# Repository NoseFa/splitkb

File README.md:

# Nordic split

A split low-profile wireless keyboard with a nordic ISO layout. I used the [Caldera Keyboard by Christian Selig](https://github.com/christianselig/caldera-keyboard) as inspiration and it clearly shows in the design. Still the keyboard uses a nice!nano like microcontroller based on the same NRF52840, ZMK as the firmware and a custom pcb with Choc V1 hotswap sockets. The keyboard also has an ortholinear layout which can be more ergonomic for some users.

The project was made and designed as a part of Hack Club's [Fallout](https://fallout.hackclub.com/) event where people make hardware projects and get a chance to go to Shenzhen, China. This was also one of my first electronics projects.

## Highlights

* Hotswapping
* Open-source
* ZMK firmware (ZMK studio support)
* Wireless
* Nordic layout
* total of 74 keys

## Why it exists?

The project was made because I wanted a split keyboard but needed a nordic layout for my day to day stuff (I need the letters Ä, Ö, Å). So the nordic split was born. I took inspiration from the Caldera keyboard by Christian Selig. It's low profile so it can be transported easily around and it's also wireless so no need for annoying dual or split cables for connecting to a computer or laptop.

This is the first keyboard I have designed so the keymap and layout were made with some educated guess work. They might be updated later down the line. I will update this repo with the most recent keymap I use. Even though it was designed as nordic layout first. The keyboard could also be used by people with non-nordic layouts and you could use the extra row of keys on the right side as shortcut or macro keys. Of course also the pcb could be edited and these keys removed if you don't want them. This keyboard has ZMK studio support so you can change the keymap in the [ZMK.studio](https://zmk.studio) web app.

## BOM summary

* Pro Micro NRF52840 [Aliexpress](https://www.aliexpress.com/item/1005007205026373.html?spm=a2g0o.productlist.main.8.5285a54cPOmIpa&aem_p4p_detail=202603200108531573820844269200000457052&algo_pvid=ebbbcca8-17d4-4ca8-b59a-75b1f3198b0b&algo_exp_id=ebbbcca8-17d4-4ca8-b59a-75b1f3198b0b-7&pdp_ext_f=%7B%22order%22%3A%22771%22%2C%22eval%22%3A%221%22%2C%22fromPage%22%3A%22search%22%7D&pdp_npi=6%40dis%21EUR%214.49%213.16%21%21%2134.88%2124.54%21%40211b813f17739941330401522ee8fd%2112000039797470328%21sea%21FI%210%21ABX%211%210%21n_tag%3A-29910%3Bd%3Ab451bb2c%3Bm03_new_user%3A-29895%3BpisId%3A5000000197850273&curPageLogUid=OxA2oroU7gov&utparam-url=scene%3Asearch%7Cquery_from%3A%7Cx_object_id%3A1005007205026373%7C_p_origin_prod%3A&search_p4p_id=202603200108531573820844269200000457052_2)
* Kailh choc v1 low-profile switches [Aliexpress](https://www.aliexpress.com/item/1005008644185126.html?spm=a2g0o.productlist.main.5.adcaQGvpQGvpZu&algo_pvid=7020f10a-7006-45f4-a42f-99f6c67908cb&algo_exp_id=7020f10a-7006-45f4-a42f-99f6c67908cb-4&pdp_ext_f=%7B%22order%22%3A%2284%22%2C%22eval%22%3A%221%22%2C%22fromPage%22%3A%22search%22%7D&pdp_npi=6%40dis%21EUR%219.09%216.67%21%21%2169.58%2151.07%21%40211b655217816346214237590eeae4%2112000046073107251%21sea%21FI%210%21ABX%211%210%21n_tag%3A-29910%3Bd%3Ab451bb2c%3Bm03_new_user%3A-29895%3BpisId%3A5000000206890820&curPageLogUid=ON5BcLwWvUu1&utparam-url=scene%3Asearch%7Cquery_from%3A%7Cx_object_id%3A1005008644185126%7C_p_origin_prod%3A)
* 304050 Lithium-Polymer battery [42Keebs.eu](https://42keebs.eu/shop/parts/lithium-polymer-battery/?attribute_size=304050%20(600%20mAh))
* Kailh Low Profile Choc hotswap sockets [Aliexpress](https://www.aliexpress.com/item/1005011893351142.html?spm=a2g0o.productlist.main.20.799300h000h08H&algo_pvid=3ed31f2b-68fe-441b-8d77-a491477a4d1e&algo_exp_id=3ed31f2b-68fe-441b-8d77-a491477a4d1e-19&pdp_ext_f=%7B%22order%22%3A%2213%22%2C%22spu_best_type%22%3A%22price%22%2C%22eval%22%3A%221%22%2C%22fromPage%22%3A%22search%22%7D&pdp_npi=6%40dis%21EUR%212.21%210.87%21%21%2116.92%216.67%21%402103894417816348652316185eb3fb%2112000056929014932%21sea%21FI%210%21ABX%211%210%21n_tag%3A-29910%3Bd%3Ab451bb2c%3Bm03_new_user%3A-29895%3BpisId%3A5000000206890820&curPageLogUid=nRsxJkAXhesI&utparam-url=scene%3Asearch%7Cquery_from%3A%7Cx_object_id%3A1005011893351142%7C_p_origin_prod%3A)
* PCB [JLCPCB](https://cart.jlcpcb.com/quote?spm=jlcpcb.Public.2006)
* M2x8mm screws [Aliexpress](https://www.aliexpress.com/item/1005006995421098.html?spm=a2g0o.productlist.main.2.57264ed6EljEJ5&algo_pvid=026d2a42-6c71-4858-96d8-406083879f60&algo_exp_id=026d2a42-6c71-4858-96d8-406083879f60-1&pdp_ext_f=%7B%22order%22%3A%2222176%22%2C%22eval%22%3A%221%22%2C%22orig_sl_item_id%22%3A%221005006995421098%22%2C%22orig_item_id%22%3A%221005006674812661%22%2C%22fromPage%22%3A%22search%22%7D&pdp_npi=6%40dis%21EUR%214.63%210.86%21%21%2136.22%216.66%21%402103956b17767083060128755e3ad9%2112000038985462862%21sea%21FI%210%21ABX%211%210%21n_tag%3A-29910%3Bd%3A2599385b%3Bm03_new_user%3A-29895%3BpisId%3A5000000205009259&curPageLogUid=HEtOGF0Rf2DI&utparam-url=scene%3Asearch%7Cquery_from%3A%7Cx_object_id%3A1005006995421098%7C_p_origin_prod%3A1005006674812661#nav-specification)
* M2 3mm OD heated inserts [Aliexpress](https://www.aliexpress.com/item/1005006071488810.html?spm=a2g0o.productlist.main.4.3d84TPXMTPXMy9&aem_p4p_detail=202606081050152534281587616560004055138&algo_pvid=06543870-17ef-47a2-afb1-9c8174047a0e&algo_exp_id=06543870-17ef-47a2-afb1-9c8174047a0e-3&pdp_ext_f=%7B%22order%22%3A%2222568%22%2C%22spu_best_type%22%3A%22price%22%2C%22eval%22%3A%221%22%2C%22fromPage%22%3A%22search%22%7D&pdp_npi=6%40dis%21EUR%212.84%211.82%21%21%2121.70%2113.93%21%40211b80d117809410151605687ea277%2112000035595774900%21sea%21FI%210%21ABX%211%210%21n_tag%3A-29910%3Bd%3Ab451bb2c%3Bm03_new_user%3A-29895%3BpisId%3A5000000207307501&curPageLogUid=m7Avo8Kp89dD&utparam-url=scene%3Asearch%7Cquery_from%3A%7Cx_object_id%3A1005006071488810%7C_p_origin_prod%3A&search_p4p_id=202606081050152534281587616560004055138_1)
* SOD-123 Diodes [Aliexpress](https://www.aliexpress.com/item/1005007536719404.html?spm=a2g0o.productlist.main.2.7a4f7cffMh3WoE&algo_pvid=ce6776f4-195e-458e-a30a-b94edfc8714d&algo_exp_id=ce6776f4-195e-458e-a30a-b94edfc8714d-1&pdp_ext_f=%7B%22order%22%3A%2294%22%2C%22eval%22%3A%221%22%2C%22fromPage%22%3A%22search%22%7D&pdp_npi=6%40dis%21EUR%211.87%211.43%21%21%2114.28%2110.91%21%40210385db17816331963967914e2c50%2112000041199095476%21sea%21FI%210%21ABX%211%210%21n_tag%3A-29910%3Bd%3Ab451bb2c%3Bm03_new_user%3A-29895%3BpisId%3A5000000207307454&curPageLogUid=43hY8FWrAoHt&utparam-url=scene%3Asearch%7Cquery_from%3A%7Cx_object_id%3A1005007536719404%7C_p_origin_prod%3A)
* Kailh choc V1 A keycaps [Aliexpress](https://www.aliexpress.com/item/1005009262759706.html?spm=a2g0o.productlist.main.34.2b272264TTHKbg&algo_pvid=d5ef2f18-90d5-413f-95b3-76c1146a87f9&algo_exp_id=d5ef2f18-90d5-413f-95b3-76c1146a87f9-33&pdp_ext_f=%7B%22order%22%3A%22207%22%2C%22eval%22%3A%221%22%2C%22fromPage%22%3A%22search%22%7D&pdp_npi=6%40dis%21EUR%2127.60%2119.32%21%21%21211.53%21148.07%21%40211b6c1717816979752355472ea7cb%2112000048523171763%21sea%21FI%210%21ABX%211%210%21n_tag%3A-29910%3Bd%3A2599385b%3Bm03_new_user%3A-29895&curPageLogUid=vcYL3e40gH5n&utparam-url=scene%3Asearch%7Cquery_from%3A%7Cx_object_id%3A1005009262759706%7C_p_origin_prod%3A)
* Anti-slip pads [Aliexpress](https://www.aliexpress.com/item/1005007438396940.html?spm=a2g0o.detail.pcDetailTopMoreOtherSeller.4.d2f1TEEKTEEKp1&gps-id=pcDetailTopMoreOtherSeller&scm=1007.40050.354490.0&scm_id=1007.40050.354490.0&scm-url=1007.40050.354490.0&pvid=88a60b80-e045-479f-a4ac-5c6461aae76d&_t=gps-id%3ApcDetailTopMoreOtherSeller%2Cscm-url%3A1007.40050.354490.0%2Cpvid%3A88a60b80-e045-479f-a4ac-5c6461aae76d%2Ctpp_buckets%3A668%232846%238112%231997&pdp_ext_f=%7B%22order%22%3A%22241%22%2C%22eval%22%3A%221%22%2C%22sceneId%22%3A%2230050%22%2C%22fromPage%22%3A%22recommend%22%7D&pdp_npi=6%40dis%21EUR%213.13%210.87%21%21%213.55%210.99%21%4021039eb717816998437457301e1070%2112000040757551361%21rec%21FI%21%21ABX%211%210%21n_tag%3A-29910%3Bd%3A2599385b%3Bm03_new_user%3A-29895%3BpisId%3A5000000206890820&utparam-url=scene%3ApcDetailTopMoreOtherSeller%7Cquery_from%3A%7Cx_object_id%3A1005007438396940%7C_p_origin_prod%3A)

Total price for the whole build excluding 3d prints is 159.26€.

You can find the full [BOM here](BOM.csv). It includes pricing, amount of parts, extra info etc.

## Build Guide Summary

1. Order PCB and other parts.
2. Order or print the case.
3. Solder parts to the PCBs (Diodes, hotswap-sockets, microcontroller)
4. Install the heated threaded inserts to the spots in the case (4 per side)
5. Install the PCB to the case.
6. Install top plate.
7. Install the choc switches to the sockets and keycaps.
8. Flash software (Check software section)
9. Enjoy!

More detailed build guide is available in the [build guide.md file](buildGuide.md).

## Software

See [Software.md](./Software/software.md) for more info about software and software installation instructions. The software source code files are in a different repo ([NoseFa/nordic-split-zmk](https://github.com/NoseFa/nordic-split-zmk))

## PCB

Here is a picture of the left side PCB. You can see the switches, traces and a spot for the microcontrollers. The PCBs are seperated by mouse bites in the middle. Unlike some other split keyboards the Nordic Splits halves aren't mirrored but instead the right side has an extra row of keys primarly needed to support the Nordic layout.

The pcb was designed in KiCad by me. You can view the files in the [Kicad folder](./KICAD/splitkb).

Here is also the schematic which is split into three different pages. One for each side and one main page that has the mousebites and links the pages together.

For ordering the PCB I used JLCPCB. You can find the gerber files as a zip in the [Production files folder](./KICAD/ProductionFiles/NordicSplitGerber.zip)

## 3D files

3d Files are seperated into 2 folders. Full project which has the .fz3 and .step versions of the whole 3D project. The PCB was exported when I finished the the edge cuts so some holes next to the micro controller might be different. I didn't include the microcontroller or the SMD diodes in the 3d project but I did check that they fit.

The 3d files for the switches in the Fusion project are from [printables](https://www.printables.com/model/716753-kaliah-choc-v1-v2-dummy/files). They are made by [cobypear](https://www.printables.com/@cobypear_1543945). They are originally from the same library as I used in kicad which is the [kiswitch library](https://github.com/kiswitch/kiswitch/tree/main/library/3dmodels/3d-library.3dshapes). You can find the original files from the link.

## Zine Page

Zine page is also available as a [PDF](./ZinePage/ZinePage.pdf).
Background picture was taken by my dad when we went up north.

## Demo

A video of the keyboard in use.

SOON (When I get the parts).

## Acknowledgements

* Thanks to [Hack Club](https://hackclub.com/) [Fallout](https://fallout.hackclub.com/). If you want to view the project I made for Fallout including journals you can view it on [the event page](https://fallout.hackclub.com/projects/156).

* [Caldera Keyboard by Christian Selig](https://github.com/christianselig/caldera-keyboard) was used as inspiration and [his video](https://www.youtube.com/watch?v=7UXsD7nSfDY) was a great watch. My design is clearly inspired by him.

## Tools used

### Design

* [KiCad](https://www.kicad.org/) (PCB design)
* [Fusion](https://www.autodesk.com/products/fusion-360/personal) (Case design)
* [Excalidraw](https://app.excalidraw.com/) (Notetaking)
* [ZMK CLI](https://zmk.dev/docs/zmk-cli) (Firmware creation)

### Assembly

* Soldering iron
* Screwdriver for the M2 screws
* Computer to flash the software.
* USB-C cable

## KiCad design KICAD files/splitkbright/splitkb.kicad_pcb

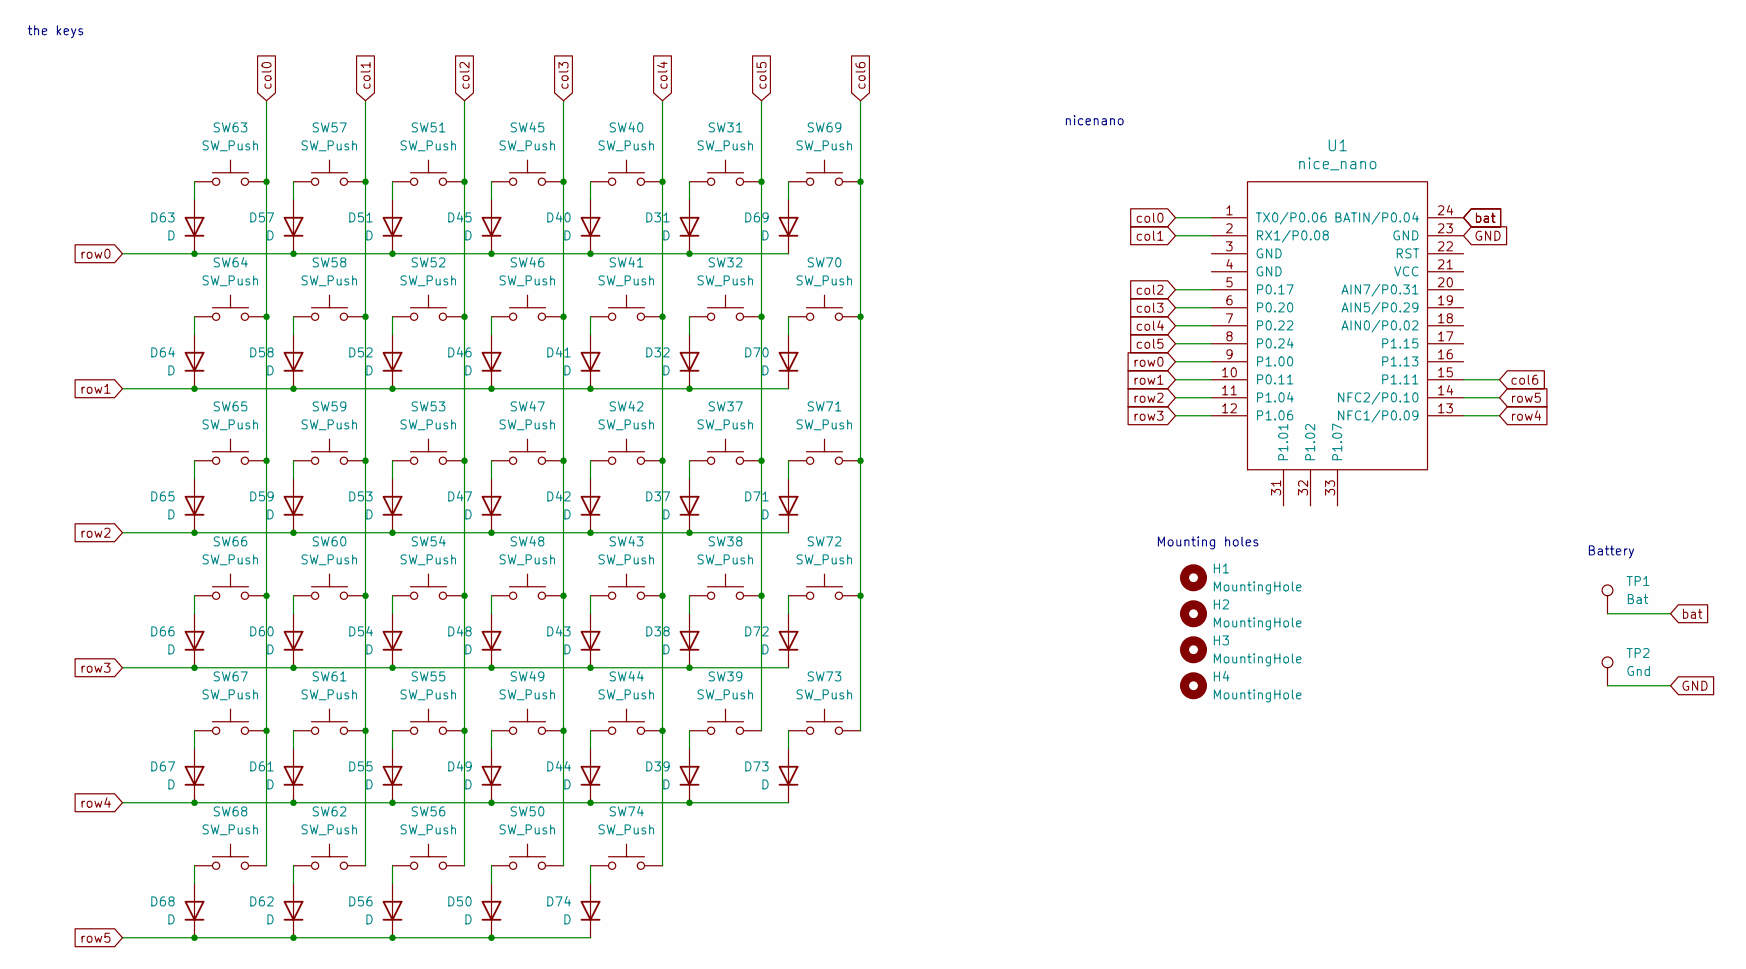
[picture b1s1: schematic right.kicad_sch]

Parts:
D31, D32, D37, D38, D39, D40, D41, D42, D43, D44, D45, D46, D47, D48, D49, D50, D51, D52, D53, D54, D55, D56, D57, D58, D59, D60, D61, D62, D63, D64, D65, D66, D67, D68, D69, D70, D71, D72, D73, D74: D; D_SOD-123
H1, H2, H3, H4: MountingHole
SW31, SW32, SW37, SW38, SW39, SW40, SW41, SW42, SW43, SW44, SW45, SW46, SW47, SW48, SW49, SW50, SW51, SW52, SW53, SW54, SW55, SW56, SW57, SW58, SW59, SW60, SW61, SW62, SW63, SW64, SW65, SW66, SW67, SW68, SW69, SW70, SW71, SW72, SW73, SW74: SW_Push; SW_Hotswap_Kailh_Choc_V1V2
TP1: Bat; TestPoint_Pad_D2.0mm
TP2: Gnd; TestPoint_Pad_D2.0mm
U1: nice_nano

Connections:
GND: TP2.1, U1.23 (GND)
unnamed: D31.2 (A), SW31.2
unnamed: D32.2 (A), SW32.2
unnamed: D37.2 (A), SW37.2
unnamed: D38.2 (A), SW38.2
unnamed: D39.2 (A), SW39.2
unnamed: D40.2 (A), SW40.2
unnamed: D41.2 (A), SW41.2
unnamed: D42.2 (A), SW42.2
unnamed: D43.2 (A), SW43.2
unnamed: D44.2 (A), SW44.2
unnamed: D45.2 (A), SW45.2
unnamed: D46.2 (A), SW46.2
unnamed: D47.2 (A), SW47.2
unnamed: D48.2 (A), SW48.2
unnamed: D49.2 (A), SW49.2
unnamed: D50.2 (A), SW50.2
unnamed: D51.2 (A), SW51.2
unnamed: D52.2 (A), SW52.2
unnamed: D53.2 (A), SW53.2
unnamed: D54.2 (A), SW54.2
unnamed: D55.2 (A), SW55.2
unnamed: D56.2 (A), SW56.2
unnamed: D57.2 (A), SW57.2
unnamed: D58.2 (A), SW58.2
unnamed: D59.2 (A), SW59.2
unnamed: D60.2 (A), SW60.2
unnamed: D61.2 (A), SW61.2
unnamed: D62.2 (A), SW62.2
unnamed: D63.2 (A), SW63.2
unnamed: D64.2 (A), SW64.2
unnamed: D65.2 (A), SW65.2
unnamed: D66.2 (A), SW66.2
unnamed: D67.2 (A), SW67.2
unnamed: D68.2 (A), SW68.2
unnamed: D69.2 (A), SW69.2
unnamed: D70.2 (A), SW70.2
unnamed: D71.2 (A), SW71.2
unnamed: D72.2 (A), SW72.2
unnamed: D73.2 (A), SW73.2
unnamed: D74.2 (A), SW74.2
bat: TP1.1, U1.24 (BATIN/P0.04)
col0: SW63.1, SW64.1, SW65.1, SW66.1, SW67.1, SW68.1, U1.1 (TX0/P0.06)
col1: SW57.1, SW58.1, SW59.1, SW60.1, SW61.1, SW62.1, U1.2 (RX1/P0.08)
col2: SW51.1, SW52.1, SW53.1, SW54.1, SW55.1, SW56.1, U1.5 (P0.17)
col3: SW45.1, SW46.1, SW47.1, SW48.1, SW49.1, SW50.1, U1.6 (P0.20)
col4: SW40.1, SW41.1, SW42.1, SW43.1, SW44.1, SW74.1, U1.7 (P0.22)
col5: SW31.1, SW32.1, SW37.1, SW38.1, SW39.1, U1.8 (P0.24)
col6: SW69.1, SW70.1, SW71.1, SW72.1, SW73.1, U1.15 (P1.11)
row0: D31.1 (K), D40.1 (K), D45.1 (K), D51.1 (K), D57.1 (K), D63.1 (K), D69.1 (K), U1.9 (P1.00)
row1: D32.1 (K), D41.1 (K), D46.1 (K), D52.1 (K), D58.1 (K), D64.1 (K), D70.1 (K), U1.10 (P0.11)
row2: D37.1 (K), D42.1 (K), D47.1 (K), D53.1 (K), D59.1 (K), D65.1 (K), D71.1 (K), U1.11 (P1.04)
row3: D38.1 (K), D43.1 (K), D48.1 (K), D54.1 (K), D60.1 (K), D66.1 (K), D72.1 (K), U1.12 (P1.06)
row4: D39.1 (K), D44.1 (K), D49.1 (K), D55.1 (K), D61.1 (K), D67.1 (K), D73.1 (K), U1.13 (NFC1/P0.09)
row5: D50.1 (K), D56.1 (K), D62.1 (K), D68.1 (K), D74.1 (K), U1.14 (NFC2/P0.10)

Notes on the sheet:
nicenano
the keys
Battery
Mounting holes

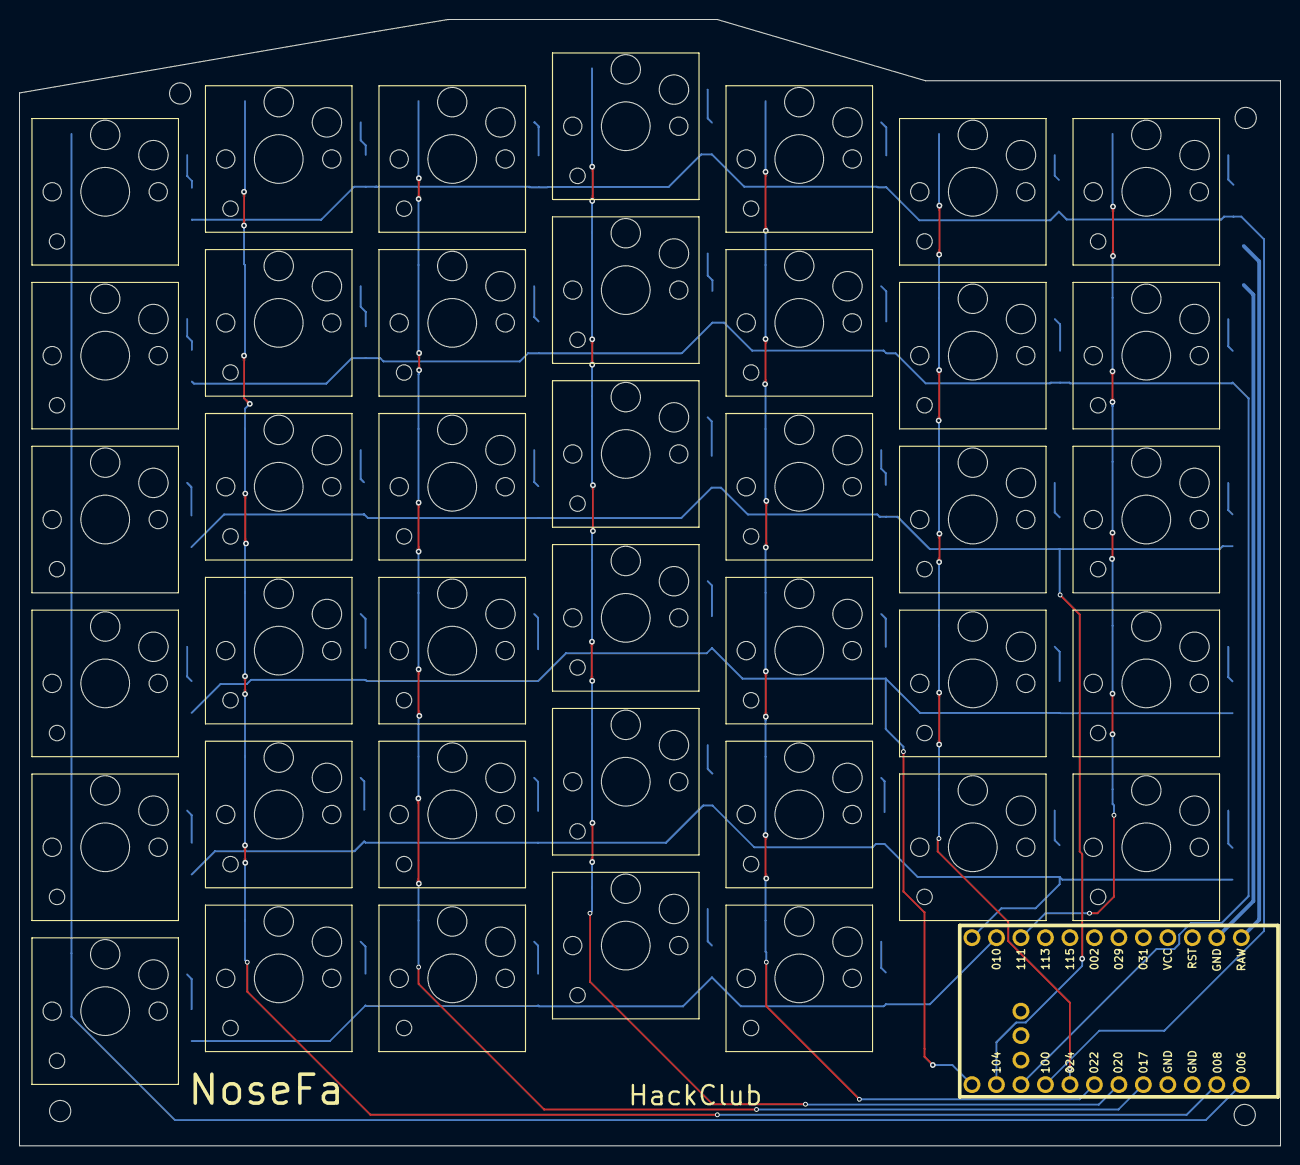
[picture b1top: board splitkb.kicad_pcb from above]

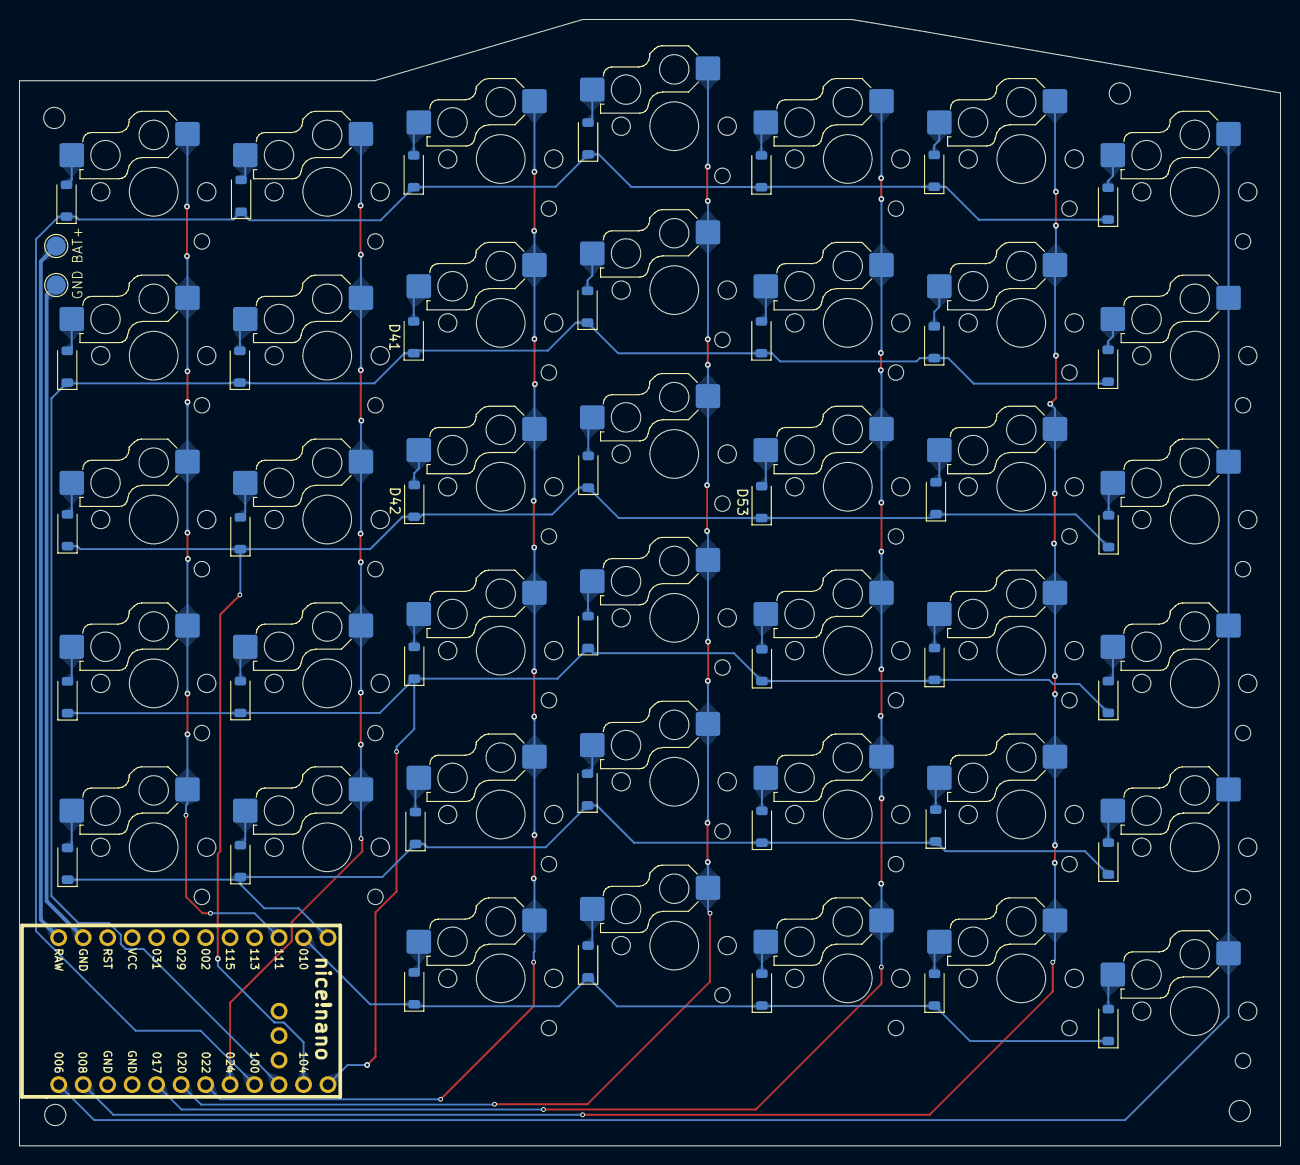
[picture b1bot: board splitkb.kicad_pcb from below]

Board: 2 copper layers, 130.8 x 116.8 mm, 83 parts (43 on the bottom side), 55 nets.

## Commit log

2026-03-16 First commit
    Moving all local files to github so they can be used by other people or me on other devices.
    Both left and right half are included.
2026-03-17 Add initial README for split keyboard project
2026-03-17 Update README.md
    Fixed a typo
2026-03-18 Revise README for Nordic split keyboard project
    Updated project description and added sections for demo and acknowledgements.
2026-03-18 Update README with firmware info and project purpose
    I added details about firmware and a section about why the project exists.
2026-03-18 Made changes to the readme and sorted stuff
    - Added pcb screenshots to the readme and media folder
    - Added the pcb files into a pcb folder for better organization.
2026-03-18 Changed README - Fixed some typos and added some info about non-nordic layout usage.
2026-03-18 Added bill of materials csv file.
2026-03-18 Changed readme to not have warnings Removed trailing spaces in readme file
2026-03-18 Fixed list in acknowledgements
2026-03-18 Ran new traces and moved controller
2026-03-18 Added key amount to README
2026-03-20 Added a DOM.csv file and deleted the placeholder.
2026-03-27 MAde changes to the cad model Made changes to the cad model and added rendered pictures of the left side
2026-03-27 Some more changes to the splitkb cad in kicad
2026-04-10 Added zine page
2026-04-10 Added a sort of thumbnail picture
2026-04-10 Added some info about zine page
2026-04-12 Edited PCBs
    - Added mounting holes to both pcbs and schematics
    - Changed the shape and size of both PCBs
2026-04-12 Changing README - Added information about how to build - Still missing information about software and assembly. - Changed some language at the start of the README.
2026-04-14 Added new zine page. - Added both sides of the keyboard to the zine page.
2026-04-20 Added info about the build guide.
    - Created software section.
    - Added info about how to build.
2026-04-20 Added screws to BOM and changed some stuff in README
2026-05-07 Edited PCB.
    - Changed the footprint used for the dev board.
    - Ran traces again for the dev board.
    - Made a custom symbol and footprint for the devboard.
2026-06-08 Changed readme to have more info.
2026-06-08 Added information about software.
2026-06-10 Changed readme about software.
2026-06-10 Edited README
2026-06-10 Changed software.md and readme. Edited kicad to v10
2026-06-12 Cleaned up the kicad project.
2026-06-12 Chnaged the name of the kicad project folder
2026-06-13 Update software documentation
2026-06-13 Move build guide
    - Move build guide from README to buildguide.md
2026-06-13 Add 3d files
    - Full project 3d files
    - 3d print 3d files
2026-06-16 Update readme and add new renders.
2026-06-16 Remove old renders.
2026-06-16 Change kicad folder name
2026-06-16 Remove old media files.
2026-06-16 Update BOM and kicad files.
2026-06-16 Add .history to gitignore
2026-06-17 Improve readme writing
2026-06-17 Update build guide
2026-06-17 Update BOM
2026-06-17 Update BOM summary
2026-06-17 Improved build instructions
2026-06-17 Add new 3d files
2026-06-17 Add ZMK studio section
2026-06-18 Add some disclaimers
2026-06-18 Add pcb order info
2026-06-18 Add shipping order info.
2026-06-19 Update flashing instructions.
2026-06-19 Update software.md with real file names
2026-06-19 Fix bom
2026-06-19 Update readme and software.md
    Add clearer notes about software source files
2026-06-19 Change wording for the note about different repo
2026-06-20 Make total price more obvious.
2026-06-20 Fix layout of BOM.
2026-06-20 Bolding fix
2026-06-20 Update total price.
2026-06-20 Self printing note
2026-06-21 Added note on about switches
2026-06-21 Add new render with switches.
2026-06-21 Add new full project files with switches.
2026-06-21 Update zine page
2026-06-21 Change Readme to explain 3d files
2026-06-21 Fix zine page exports
2026-06-23 Update prices in BOM.
2026-06-23 Update prices in BOM
2026-06-23 Updated 3d models
2026-06-23 Add MIT License
2026-06-23 Change license
2026-06-23 Update battery position in left side
